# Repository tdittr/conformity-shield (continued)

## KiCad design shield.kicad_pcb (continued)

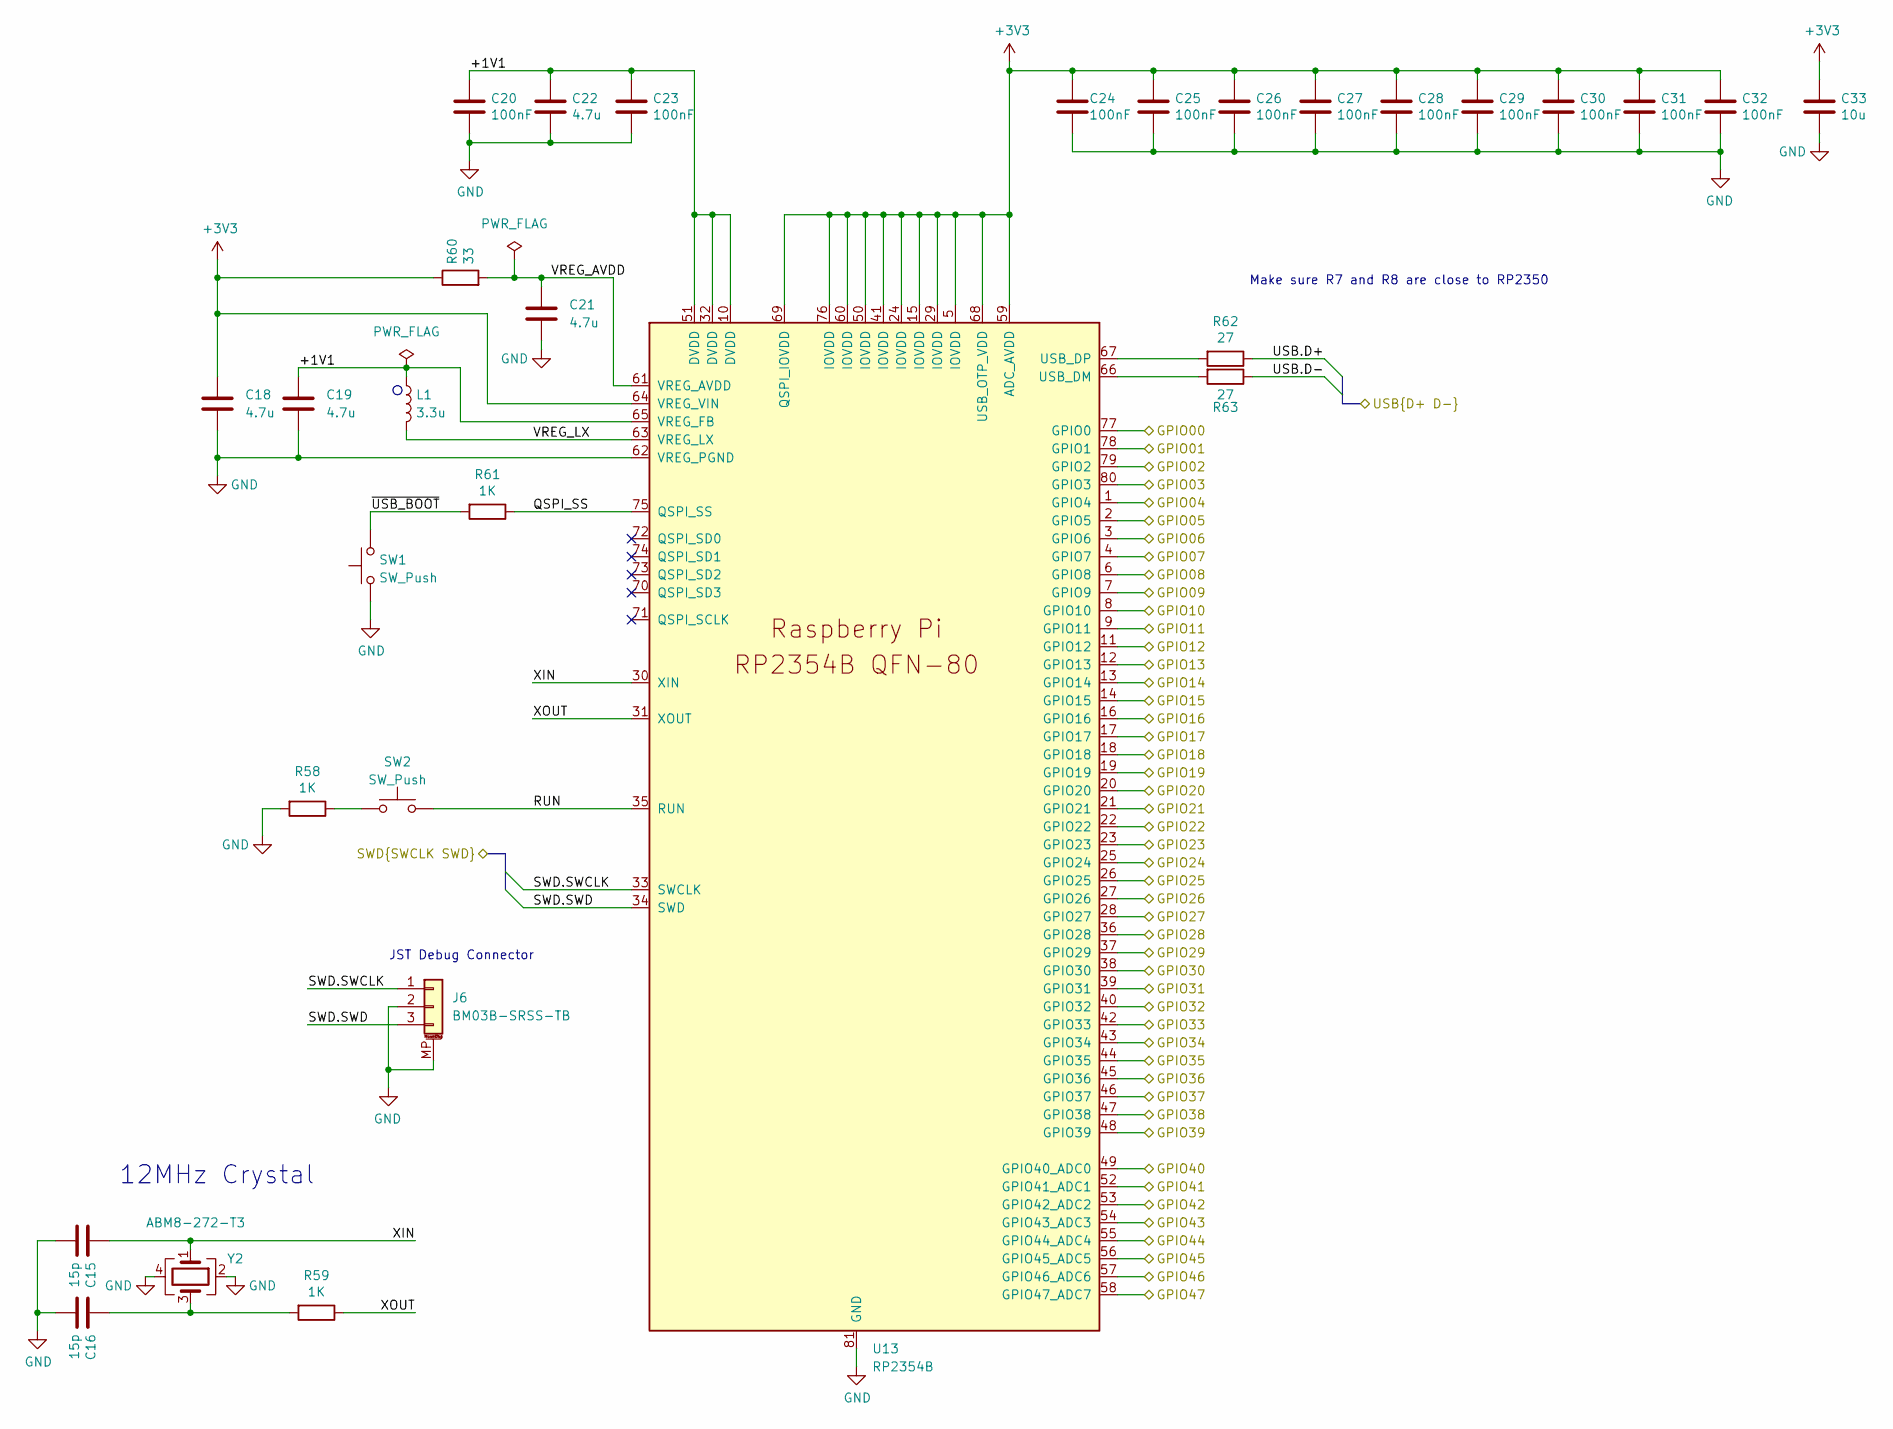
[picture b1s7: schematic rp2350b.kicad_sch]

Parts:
C15, C16: 15p; C_0402_1005Metric; LCSC C1548
C18, C19: 4.7u; C_0402_1005Metric_small_pads; LCSC C23733
C20, C23, C24, C25, C26, C27, C28, C29, C30, C31, C32: 100nF; C_0402_1005Metric; LCSC C1525
C21, C22: 4.7u; C_0402_1005Metric; LCSC C23733
C33: 10u; C_0805_2012Metric; LCSC C15850
J6: BM03B-SRSS-TB; JST_SH_BM03B-SRSS-TB_1x03-1MP_P1.00mm_Vertical; LCSC C160389
L1: 3.3u; L_pol_2016; LCSC C42411119
R58, R59, R61: 1K; R_0402_1005Metric; LCSC C11702
R60: 33; R_0402_1005Metric; LCSC C25105
R62, R63: 27; R_0402_1005Metric; LCSC C138021
SW1, SW2: SW_Push; SW_Push_1P1T_XKB_TS-1187A; LCSC C318884
U13: RP2354B; QFN-80-1EP_10x10mm_P0.4mm_EP3.4x3.4mm_ThermalVias; LCSC C39843328
Y2: ABM8-272-T3; Crystal_SMD_3225-4Pin_3.2x2.5mm; LCSC C20625731

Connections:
+3V3: C18.1, C24.1, C25.1, C26.1, C27.1, C28.1, C29.1, C30.1, C31.1, C32.1, C33.1, R60.1, U13.5 (IOVDD), U13.15 (IOVDD), U13.24 (IOVDD), U13.29 (IOVDD), U13.41 (IOVDD), U13.50 (IOVDD), U13.59 (ADC_AVDD), U13.60 (IOVDD), U13.64 (VREG_VIN), U13.68 (USB_OTP_VDD), U13.69 (QSPI_IOVDD), U13.76 (IOVDD); also elsewhere on the board
/Tester/A0: U13.49 (GPIO40_ADC0); also elsewhere on the board
/Tester/A1: U13.52 (GPIO41_ADC1); also elsewhere on the board
/Tester/A2: U13.53 (GPIO42_ADC2); also elsewhere on the board
/Tester/A3: U13.54 (GPIO43_ADC3); also elsewhere on the board
/Tester/A4: U13.55 (GPIO44_ADC4); also elsewhere on the board
/Tester/A5: U13.56 (GPIO45_ADC5); also elsewhere on the board
/Tester/A6: U13.57 (GPIO46_ADC6); also elsewhere on the board
/Tester/D0: U13.77 (GPIO0); also elsewhere on the board
/Tester/D1: U13.78 (GPIO1); also elsewhere on the board
/Tester/D2: U13.79 (GPIO2); also elsewhere on the board
/Tester/D3: U13.80 (GPIO3); also elsewhere on the board
/Tester/D4: U13.1 (GPIO4); also elsewhere on the board
/Tester/D5: U13.2 (GPIO5); also elsewhere on the board
/Tester/D6: U13.3 (GPIO6); also elsewhere on the board
/Tester/D7: U13.4 (GPIO7); also elsewhere on the board
/Tester/D8: U13.6 (GPIO8); also elsewhere on the board
/Tester/D9: U13.7 (GPIO9); also elsewhere on the board
/Tester/D10: U13.8 (GPIO10), U13.26 (GPIO25); also elsewhere on the board
/Tester/D11: U13.9 (GPIO11), U13.25 (GPIO24); also elsewhere on the board
/Tester/D12: U13.11 (GPIO12), U13.28 (GPIO27); also elsewhere on the board
/Tester/D13: U13.12 (GPIO13), U13.27 (GPIO26); also elsewhere on the board
/Tester/D14: U13.13 (GPIO14); also elsewhere on the board
/Tester/D15: U13.14 (GPIO15); also elsewhere on the board
/Tester/EN_USB_0: U13.20 (GPIO20); also elsewhere on the board
/Tester/EN_USB_1: U13.22 (GPIO22); also elsewhere on the board
/Tester/FLAG_USB_0: U13.21 (GPIO21); also elsewhere on the board
/Tester/FLAG_USB_1: U13.23 (GPIO23); also elsewhere on the board
/Tester/HD+: U13.18 (GPIO18); also elsewhere on the board
/Tester/HD-: U13.19 (GPIO19); also elsewhere on the board
/Tester/I2C.SCL: U13.39 (GPIO31); also elsewhere on the board
/Tester/I2C.SDA: U13.38 (GPIO30); also elsewhere on the board
/Tester/PWM0: U13.48 (GPIO39); also elsewhere on the board
/Tester/PWM1: U13.47 (GPIO38); also elsewhere on the board
/Tester/PWM2: U13.46 (GPIO37); also elsewhere on the board
/Tester/PWM3: U13.45 (GPIO36); also elsewhere on the board
/Tester/PWM4: U13.44 (GPIO35); also elsewhere on the board
/Tester/PWM5: U13.43 (GPIO34); also elsewhere on the board
/Tester/PWM6: U13.42 (GPIO33); also elsewhere on the board
/Tester/RP2350B/+1V1: C19.1, C20.1, C22.1, C23.1, L1.1, U13.10 (DVDD), U13.32 (DVDD), U13.51 (DVDD), U13.65 (VREG_FB)
/Tester/RP2350B/GPIO47: U13.58 (GPIO47_ADC7); also elsewhere on the board
/Tester/RP2350B/QSPI_SS: R61.1, U13.75 (QSPI_SS)
/Tester/RP2350B/RUN: SW2.2, U13.35 (RUN)
/Tester/RP2350B/VREG_AVDD: C21.1, R60.2, U13.61 (VREG_AVDD)
/Tester/RP2350B/VREG_LX: L1.2, U13.63 (VREG_LX)
/Tester/RP2350B/XIN: C15.1, U13.30 (XIN), Y2.1
/Tester/RP2350B/XOUT: R59.1, U13.31 (XOUT)
/Tester/RP2350B/~USB_BOOT: R61.2, SW1.2
/Tester/SWD.SWCLK: J6.1, U13.33 (SWCLK); also elsewhere on the board
/Tester/SWD.SWD: J6.3, U13.34 (SWD); also elsewhere on the board
/Tester/TIDO: U13.37 (GPIO29); also elsewhere on the board
/Tester/TODI: U13.36 (GPIO28); also elsewhere on the board
/Tester/USB.D+: R62.1; also elsewhere on the board
/Tester/USB.D-: R63.1; also elsewhere on the board
/Tester/USBH_SEL: U13.17 (GPIO17); also elsewhere on the board
/Tester/~TARGET_RESET: U13.40 (GPIO32); also elsewhere on the board
/Tester/~USBH_EN: U13.16 (GPIO16); also elsewhere on the board
GND: C15.2, C16.2, C18.2, C19.2, C20.2, C21.2, C22.2, C23.2, C24.2, C25.2, C26.2, C27.2, C28.2, C29.2, C30.2, C31.2, C32.2, C33.2, J6.2, J6.MP (MountPin), R58.2, SW1.1, U13.62 (VREG_PGND), U13.81 (GND), Y2.2, Y2.4; also elsewhere on the board
unnamed: C16.1, R59.2, Y2.3
unnamed: R58.1, SW2.1
unnamed: R63.2, U13.66 (USB_DM)
unnamed: R62.2, U13.67 (USB_DP)

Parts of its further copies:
C14, C17: 15p; C_0402_1005Metric; LCSC C1548
C34, C35: 4.7u; C_0402_1005Metric_small_pads; LCSC C23733
C36, C39, C40, C41, C42, C43, C44, C45, C46, C47, C48: 100nF; C_0402_1005Metric; LCSC C1525
C37, C38: 4.7u; C_0402_1005Metric; LCSC C23733
C49: 10u; C_0805_2012Metric; LCSC C15850
J4: BM03B-SRSS-TB; JST_SH_BM03B-SRSS-TB_1x03-1MP_P1.00mm_Vertical; LCSC C160389
L2: 3.3u; L_pol_2016; LCSC C42411119
R57, R64, R66: 1K; R_0402_1005Metric; LCSC C11702
R65: 33; R_0402_1005Metric; LCSC C25105
R67, R68: 27; R_0402_1005Metric; LCSC C138021
SW3, SW4: SW_Push; SW_Push_1P1T_XKB_TS-1187A; LCSC C318884
U12: RP2354B; QFN-80-1EP_10x10mm_P0.4mm_EP3.4x3.4mm_ThermalVias; LCSC C39843328
Y3: ABM8-272-T3; Crystal_SMD_3225-4Pin_3.2x2.5mm; LCSC C20625731

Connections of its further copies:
+3V3: C34.1, C40.1, C41.1, C42.1, C43.1, C44.1, C45.1, C46.1, C47.1, C48.1, C49.1, R65.1, U12.5 (IOVDD), U12.15 (IOVDD), U12.24 (IOVDD), U12.29 (IOVDD), U12.41 (IOVDD), U12.50 (IOVDD), U12.59 (ADC_AVDD), U12.60 (IOVDD), U12.64 (VREG_VIN), U12.68 (USB_OTP_VDD), U12.69 (QSPI_IOVDD), U12.76 (IOVDD); also elsewhere on the board
/Tester/SWD.SWCLK: U12.8 (GPIO10); also elsewhere on the board
/Tester/SWD.SWD: U12.9 (GPIO11); also elsewhere on the board
/Tester/TIDO: U12.11 (GPIO12); also elsewhere on the board
/Tester/TODI: U12.12 (GPIO13); also elsewhere on the board
/USB/USB4.D+: R67.1; also elsewhere on the board
/USB/USB4.D-: R68.1; also elsewhere on the board
/debugger/GNDDetect: U12.77 (GPIO0); also elsewhere on the board
/debugger/RP2350B1/+1V1: C35.1, C36.1, C38.1, C39.1, L2.1, U12.10 (DVDD), U12.32 (DVDD), U12.51 (DVDD), U12.65 (VREG_FB)
/debugger/RP2350B1/GPIO14: U12.13 (GPIO14)
/debugger/RP2350B1/GPIO15: U12.14 (GPIO15)
/debugger/RP2350B1/GPIO16: U12.16 (GPIO16)
/debugger/RP2350B1/GPIO17: U12.17 (GPIO17)
/debugger/RP2350B1/GPIO18: U12.18 (GPIO18)
/debugger/RP2350B1/GPIO19: U12.19 (GPIO19)
/debugger/RP2350B1/GPIO20: U12.20 (GPIO20)
/debugger/RP2350B1/GPIO21: U12.21 (GPIO21)
/debugger/RP2350B1/GPIO22: U12.22 (GPIO22)
/debugger/RP2350B1/GPIO23: U12.23 (GPIO23)
/debugger/RP2350B1/GPIO24: U12.25 (GPIO24)
/debugger/RP2350B1/GPIO25: U12.26 (GPIO25); also elsewhere on the board
/debugger/RP2350B1/GPIO26: U12.27 (GPIO26)
/debugger/RP2350B1/GPIO27: U12.28 (GPIO27)
/debugger/RP2350B1/GPIO28: U12.36 (GPIO28)
/debugger/RP2350B1/GPIO29: U12.37 (GPIO29)
/debugger/RP2350B1/GPIO30: U12.38 (GPIO30)
/debugger/RP2350B1/GPIO31: U12.39 (GPIO31)
/debugger/RP2350B1/GPIO32: U12.40 (GPIO32)
/debugger/RP2350B1/GPIO33: U12.42 (GPIO33)
/debugger/RP2350B1/GPIO34: U12.43 (GPIO34)
/debugger/RP2350B1/GPIO35: U12.44 (GPIO35)
/debugger/RP2350B1/GPIO36: U12.45 (GPIO36)
/debugger/RP2350B1/GPIO37: U12.46 (GPIO37)
/debugger/RP2350B1/GPIO38: U12.47 (GPIO38)
/debugger/RP2350B1/GPIO39: U12.48 (GPIO39)
/debugger/RP2350B1/GPIO41: U12.52 (GPIO41_ADC1)
/debugger/RP2350B1/GPIO42: U12.53 (GPIO42_ADC2)
/debugger/RP2350B1/GPIO43: U12.54 (GPIO43_ADC3)
/debugger/RP2350B1/GPIO44: U12.55 (GPIO44_ADC4)
/debugger/RP2350B1/GPIO45: U12.56 (GPIO45_ADC5)
/debugger/RP2350B1/GPIO46: U12.57 (GPIO46_ADC6)
/debugger/RP2350B1/GPIO47: U12.58 (GPIO47_ADC7)
/debugger/RP2350B1/QSPI_SS: R66.1, U12.75 (QSPI_SS)
/debugger/RP2350B1/RUN: SW4.2, U12.35 (RUN)
/debugger/RP2350B1/SWD.SWCLK: J4.1, U12.33 (SWCLK)
/debugger/RP2350B1/SWD.SWD: J4.3, U12.34 (SWD)
/debugger/RP2350B1/VREG_AVDD: C37.1, R65.2, U12.61 (VREG_AVDD)
/debugger/RP2350B1/VREG_LX: L2.2, U12.63 (VREG_LX)
/debugger/RP2350B1/XIN: C14.1, U12.30 (XIN), Y3.1
/debugger/RP2350B1/XOUT: R64.1, U12.31 (XOUT)
/debugger/RP2350B1/~USB_BOOT: R66.2, SW3.2
/debugger/SCL: U12.7 (GPIO9); also elsewhere on the board
/debugger/SDA: U12.6 (GPIO8); also elsewhere on the board
/debugger/SWCLK: U12.79 (GPIO2); also elsewhere on the board
/debugger/SWD: U12.80 (GPIO3); also elsewhere on the board
/debugger/SWO: U12.4 (GPIO7); also elsewhere on the board
/debugger/TARGET_RX: U12.2 (GPIO5); also elsewhere on the board
/debugger/TARGET_TX: U12.1 (GPIO4); also elsewhere on the board
/debugger/TDI: U12.3 (GPIO6); also elsewhere on the board
/debugger/Vref: U12.49 (GPIO40_ADC0); also elsewhere on the board
/debugger/~TARGET_RESET: U12.78 (GPIO1); also elsewhere on the board
GND: C14.2, C17.2, C34.2, C35.2, C36.2, C37.2, C38.2, C39.2, C40.2, C41.2, C42.2, C43.2, C44.2, C45.2, C46.2, C47.2, C48.2, C49.2, J4.2, J4.MP (MountPin), R57.2, SW3.1, U12.62 (VREG_PGND), U12.81 (GND), Y3.2, Y3.4; also elsewhere on the board
unnamed: C17.1, R64.2, Y3.3
unnamed: R57.1, SW4.1
unnamed: R68.2, U12.66 (USB_DM)
unnamed: R67.2, U12.67 (USB_DP)

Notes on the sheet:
12MHz Crystal
Make sure R7 and R8 are close to RP2350
JST Debug Connector

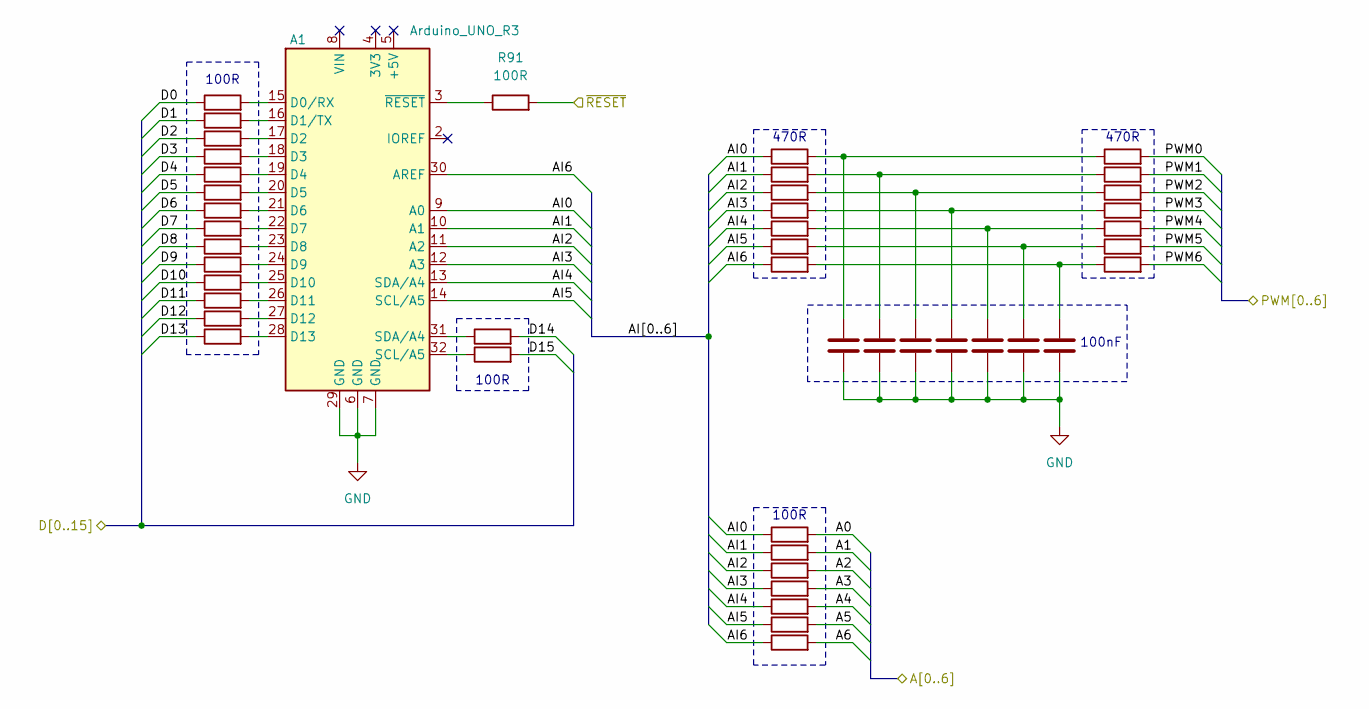
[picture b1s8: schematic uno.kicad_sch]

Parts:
A1: Arduino_UNO_R3; Arduino_UNO_R3_ShieldBase
C5, C6, C7, C8, C9, C10, C11: 100nF; C_0402_1005Metric_Pad0.74x0.62mm_HandSolder; LCSC C1525
R16, R17, R18, R19, R20, R21, R22, R23, R24, R25, R26, R27, R28, R29, R30, R31, R39, R40, R41, R42, R43, R44, R45, R91: 100R; R_0402_1005Metric_Pad0.72x0.64mm_HandSolder; LCSC C25076
R32, R33, R34, R35, R36, R37, R38, R46, R47, R48, R49, R50, R51, R52: 470R; R_0402_1005Metric_Pad0.72x0.64mm_HandSolder; LCSC C25117

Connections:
/Tester/A0: R39.2; also elsewhere on the board
/Tester/A1: R40.2; also elsewhere on the board
/Tester/A2: R41.2; also elsewhere on the board
/Tester/A3: R42.2; also elsewhere on the board
/Tester/A4: R43.2; also elsewhere on the board
/Tester/A5: R44.2; also elsewhere on the board
/Tester/A6: R45.2; also elsewhere on the board
/Tester/D0: R16.1; also elsewhere on the board
/Tester/D1: R17.1; also elsewhere on the board
/Tester/D2: R18.1; also elsewhere on the board
/Tester/D3: R19.1; also elsewhere on the board
/Tester/D4: R20.1; also elsewhere on the board
/Tester/D5: R21.1; also elsewhere on the board
/Tester/D6: R22.1; also elsewhere on the board
/Tester/D7: R23.1; also elsewhere on the board
/Tester/D8: R24.1; also elsewhere on the board
/Tester/D9: R25.1; also elsewhere on the board
/Tester/D10: R26.1; also elsewhere on the board
/Tester/D11: R27.1; also elsewhere on the board
/Tester/D12: R28.1; also elsewhere on the board
/Tester/D13: R29.1; also elsewhere on the board
/Tester/D14: R30.2; also elsewhere on the board
/Tester/D15: R31.2; also elsewhere on the board
/Tester/PWM0: R46.2; also elsewhere on the board
/Tester/PWM1: R47.2; also elsewhere on the board
/Tester/PWM2: R48.2; also elsewhere on the board
/Tester/PWM3: R49.2; also elsewhere on the board
/Tester/PWM4: R50.2; also elsewhere on the board
/Tester/PWM5: R51.2; also elsewhere on the board
/Tester/PWM6: R52.2; also elsewhere on the board
/Tester/uno/AI0: A1.9 (A0), R32.1, R39.1
/Tester/uno/AI1: A1.10 (A1), R33.1, R40.1
/Tester/uno/AI2: A1.11 (A2), R34.1, R41.1
/Tester/uno/AI3: A1.12 (A3), R35.1, R42.1
/Tester/uno/AI4: A1.13 (SDA/A4), R36.1, R43.1
/Tester/uno/AI5: A1.14 (SCL/A5), R37.1, R44.1
/Tester/uno/AI6: A1.30 (AREF), R38.1, R45.1
/Tester/~TARGET_RESET: R91.2; also elsewhere on the board
GND: A1.6 (GND), A1.7 (GND), A1.29 (GND), C5.2, C6.2, C7.2, C8.2, C9.2, C10.2, C11.2; also elsewhere on the board
unnamed: A1.15 (D0/RX), R16.2
unnamed: A1.16 (D1/TX), R17.2
unnamed: A1.17 (D2), R18.2
unnamed: A1.18 (D3), R19.2
unnamed: A1.19 (D4), R20.2
unnamed: A1.20 (D5), R21.2
unnamed: A1.21 (D6), R22.2
unnamed: A1.22 (D7), R23.2
unnamed: A1.23 (D8), R24.2
unnamed: A1.24 (D9), R25.2
unnamed: A1.25 (D10), R26.2
unnamed: A1.26 (D11), R27.2
unnamed: A1.27 (D12), R28.2
unnamed: A1.28 (D13), R29.2
unnamed: A1.32 (SCL/A5), R31.1
unnamed: A1.31 (SDA/A4), R30.1
unnamed: A1.3 (~RESET), R91.1
unnamed: C5.1, R32.2, R46.1
unnamed: C6.1, R33.2, R47.1
unnamed: C7.1, R34.2, R48.1
unnamed: C8.1, R35.2, R49.1
unnamed: C9.1, R36.2, R50.1
unnamed: C10.1, R37.2, R51.1
unnamed: C11.1, R38.2, R52.1

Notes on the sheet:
470R
100R
100nF

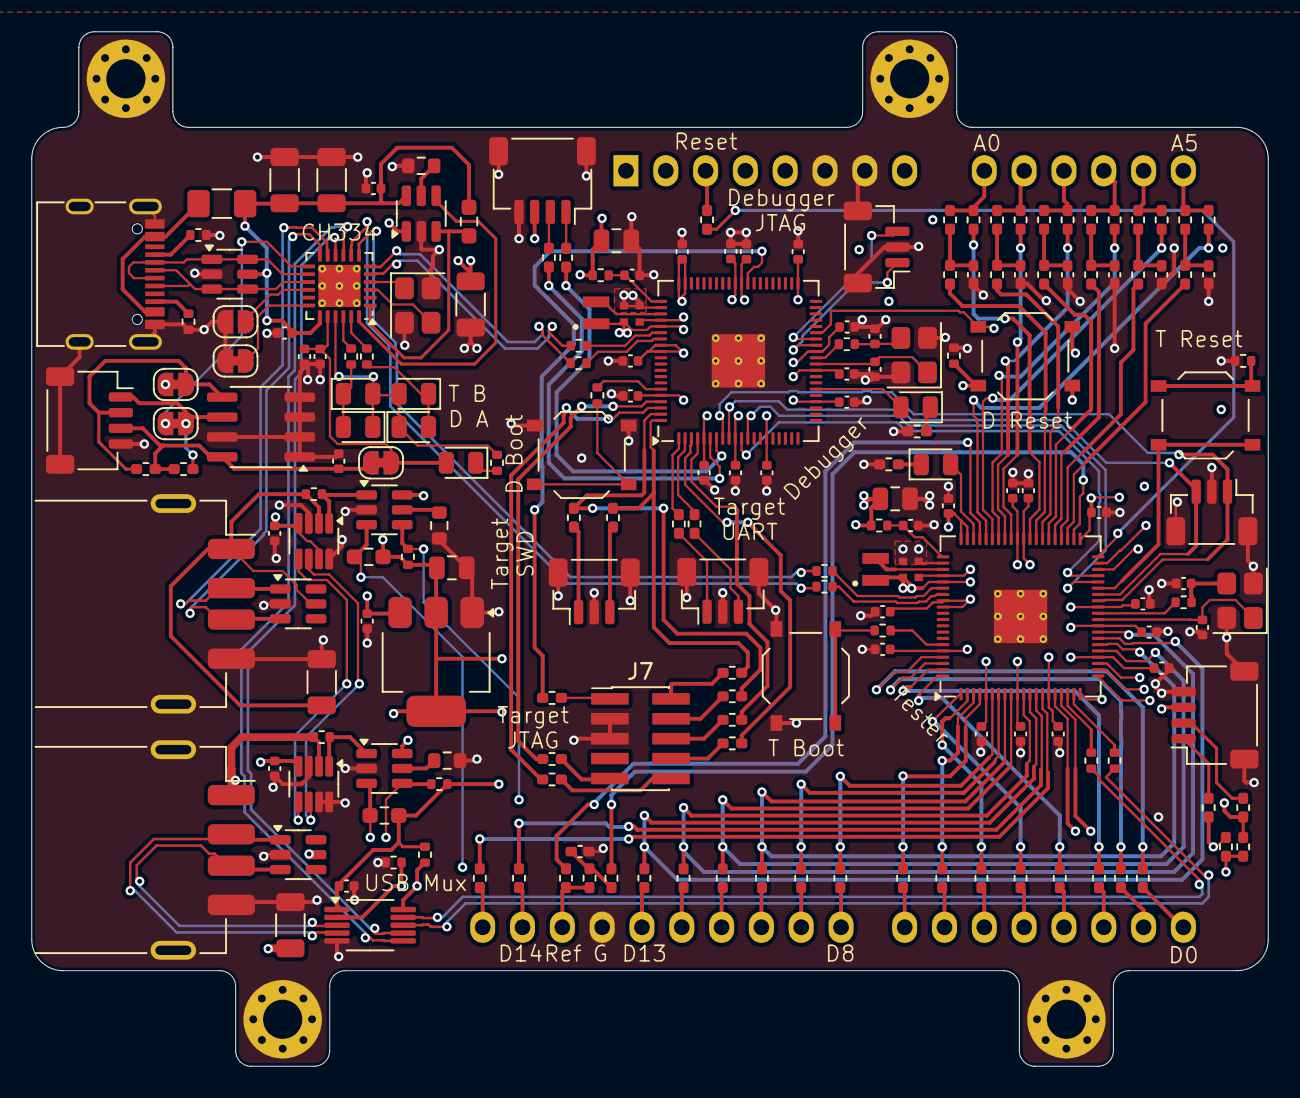
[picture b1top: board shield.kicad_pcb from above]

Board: 4 copper layers, 78.9 x 66.0 mm, 200 parts (0 on the bottom side), 177 nets.

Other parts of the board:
H1#2, H3#2: MountingHole_Pad; MountingHole_2.5mm_Pad_Via

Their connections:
GND: H1#2.1, H3#2.1; also elsewhere on the board

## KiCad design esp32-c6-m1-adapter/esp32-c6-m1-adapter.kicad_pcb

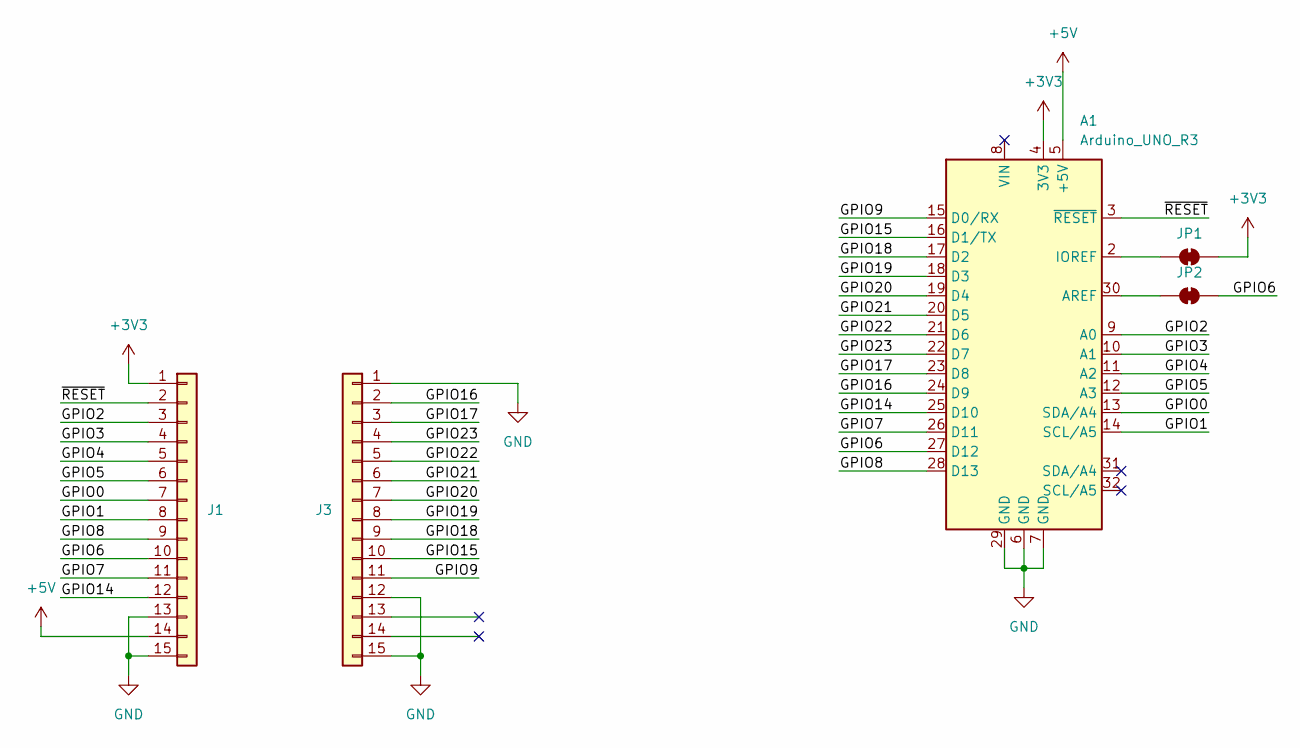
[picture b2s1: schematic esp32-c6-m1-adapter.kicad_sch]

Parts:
A1: Arduino_UNO_R3; Arduino_UNO_R3_ShieldBase
J1, J3: Conn_01x15; PinHeader_1x15_P2.54mm_Vertical
JP1, JP2: SolderJumper_2_Bridged; SolderJumper-2_P1.3mm_Bridged_RoundedPad1.0x1.5mm

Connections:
+3V3: A1.4 (3V3), J1.1, JP1.2 (B)
+5V: A1.5 (+5V), J1.14
/GPIO0: A1.13 (SDA/A4), J1.7
/GPIO1: A1.14 (SCL/A5), J1.8
/GPIO2: A1.9 (A0), J1.3
/GPIO3: A1.10 (A1), J1.4
/GPIO4: A1.11 (A2), J1.5
/GPIO5: A1.12 (A3), J1.6
/GPIO6: A1.27 (D12), J1.10, JP2.2 (B)
/GPIO7: A1.26 (D11), J1.11
/GPIO8: A1.28 (D13), J1.9
/GPIO9: A1.15 (D0/RX), J3.11
/GPIO14: A1.25 (D10), J1.12
/GPIO15: A1.16 (D1/TX), J3.10
/GPIO16: A1.24 (D9), J3.2
/GPIO17: A1.23 (D8), J3.3
/GPIO18: A1.17 (D2), J3.9
/GPIO19: A1.18 (D3), J3.8
/GPIO20: A1.19 (D4), J3.7
/GPIO21: A1.20 (D5), J3.6
/GPIO22: A1.21 (D6), J3.5
/GPIO23: A1.22 (D7), J3.4
/~RESET: A1.3 (~RESET), J1.2
GND: A1.6 (GND), A1.7 (GND), A1.29 (GND), J1.13, J1.15, J3.1, J3.12, J3.15
unnamed: A1.30 (AREF), JP2.1 (A)
unnamed: A1.2 (IOREF), JP1.1 (A)

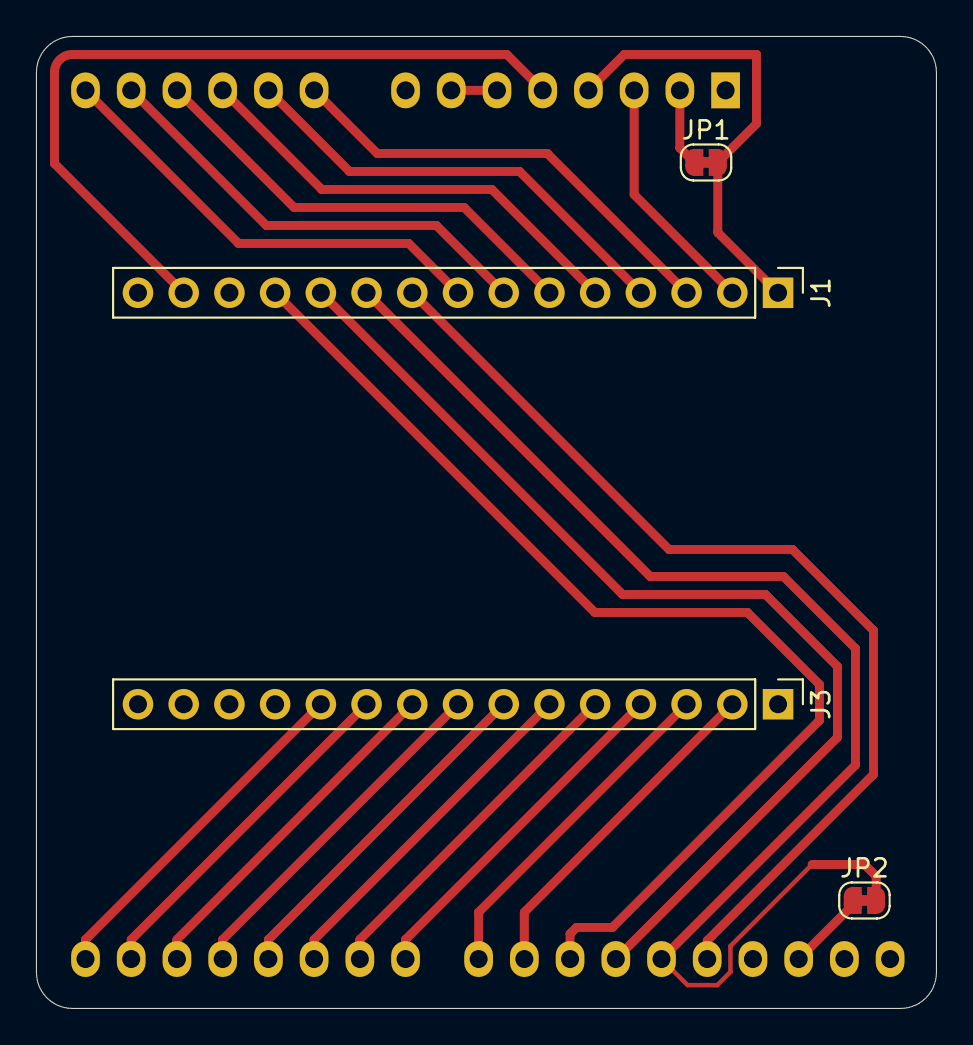
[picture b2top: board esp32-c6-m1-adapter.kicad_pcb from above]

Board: 2 copper layers, 50.0 x 54.0 mm, 5 parts (1 on the bottom side), 26 nets.

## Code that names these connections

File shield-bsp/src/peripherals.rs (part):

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    pub usb1_en: Peri<'static, PIN_22>,
    pub usb1_flag: Peri<'static, PIN_23>,

    pub todi: Peri<'static, PIN_28>,
    pub tido: Peri<'static, PIN_29>,

    pub sda: Peri<'static, PIN_30>,
    pub scl: Peri<'static, PIN_31>,
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        PIN_46,
        PIN_47,
        PIN_QSPI_SCLK: _,
        PIN_QSPI_SS: _,
        PIN_QSPI_SD0: _,
        PIN_QSPI_SD1: _,
        PIN_QSPI_SD2: _,
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            usb0_flag: PIN_21,
            usb1_en: PIN_22,
            usb1_flag: PIN_23,
            todi: PIN_28,
            tido: PIN_29,
            sda: PIN_30,
            scl: PIN_31,
            led: PIN_47,
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    usb0_flag = 21,
    usb1_en = 22,
    usb1_flag = 23,
    todi = 28,
    tido = 29,
    sda = 30,
    scl = 31,
    led = 47,
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            21 => PinName::usb0_flag,
            22 => PinName::usb1_en,
            23 => PinName::usb1_flag,
            28 => PinName::todi,
            29 => PinName::tido,
            30 => PinName::sda,
            31 => PinName::scl,
            47 => PinName::led,
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
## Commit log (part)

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2025-07-25 Initial draft for USB hub
2025-07-25 Add Uno shield
2025-08-18 Add RP2350B from example
2025-08-22 Break out RP2350
2025-08-25 Do pin assignment for tester
2025-08-27 Start Layout
2025-08-29 Layout Tester and USB Hub
2025-09-18 finished routing
2025-09-19 layout finished
2025-09-19 JLC rotations
2025-09-19 Fix JTAG IDC
2025-09-19 Finished JLC setup
2025-09-19 Add ESP32-C6 adapter
2025-10-17 Add a license and readme
2026-01-23 Fix rev1 errors
    Add USB mux to allow for USB PIO
    Fix D+ D- mixup
    Fix USB Hub LED indicator label
2026-03-09 Address board review comments
    - Add pull-ups for both I2C busses (4K7)
    - Set eFuse limit to 600mA (400mA before)
    - Label StemmaQt as such in schematics
    - Fix typo in USB Port value
    - Fix USB Mux to be disabled by default (pull-down to pull-up)
2026-03-09 Make printing pin names nicer
2026-03-09 Start BSP
2026-03-09 Split peripherals and implement board initialization
